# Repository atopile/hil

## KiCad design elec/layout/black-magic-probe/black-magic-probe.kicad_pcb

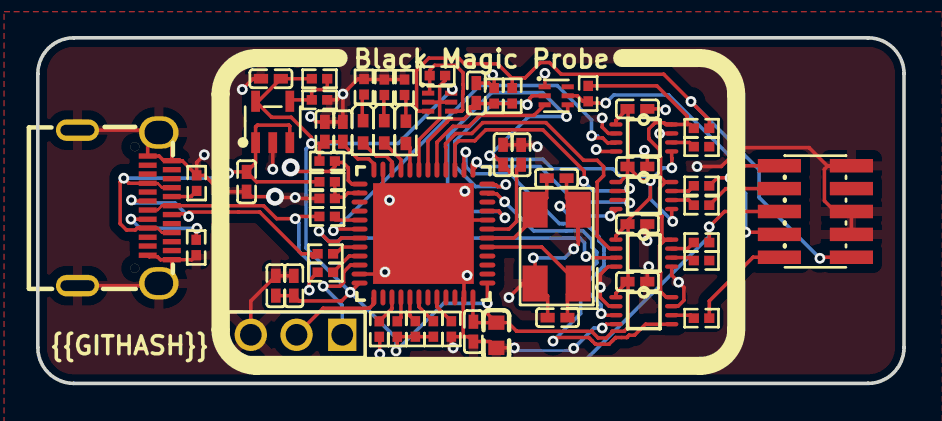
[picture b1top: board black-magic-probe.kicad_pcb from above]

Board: 2 copper layers, 48.1 x 19.2 mm, 61 parts (0 on the bottom side), 54 nets.

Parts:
C1, C2, C3, C4, C7, C8, C9, C10, C11, C12: 100nF ±10% 50V X7R; C0402-b3ef17
C5: 4.7µF ±10% 25V X5R; C0603-bd72f6
C6, C16, C17: 1µF ±10% 25V X5R; C0402-b3ef17
C13, C14: 18pF ±5% 50V C0G; C0402-b3ef17
C15: 100nF ±10% 16V X7R; C0402-b3ef17
D1, D2, D3: LED0402-R-RD-049f90
H1: HDR-TH_3P-P2.54-V-M-1-04b1f3
R1, R2, R3, R7, R11, R12, R13, R21, R23: 10kΩ ±1% 62.5mW; R0402-56259e
R4, R5, R6, R26: 1kΩ ±1% 62.5mW; R0402-56259e
R8: 1.5kΩ ±1% 62.5mW; R0402-56259e
R9, R10: 22Ω ±1% 62.5mW; R0402-56259e
R14, R15, R16, R17, R18, R19, R20, R25: 100Ω ±1% 62.5mW; R0402-56259e
R22, R24: 4.7kΩ ±1% 62.5mW; R0402-56259e
R27: 1.8kΩ ±1% 62.5mW; R0402-56259e
R28, R29: 5.1kΩ ±1% 62.5mW; R0402-56259e
U1, U2, U3, U4: VSSOP-8_L2.4-W2.1-P0.50-LS3.2-BR-acd3fc
U5: UFQFPN-48_L7.0-W7.0-P0.50-BL-EP5.6-10abf8
U6, U7: SOT-563-6_L1.6-W1.2-P0.5-LS1.6-BL-d9216f
U8: HDR-SMD_10P-P1.27-V-M-R2-C5-LS5.3-41d9cc
U9: SOT-23-5_L3.0-W1.7-P0.95-LS2.8-BL
USB1: USB-C-SMD_TYC-324G-a50b79
X1: OSC-SMD_4P-L5.0-W3.2-BL-ee849f

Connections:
ADJ_NC: R26.1, R27.2, U9.4
B5: R29.1, USB1.B5
BOOT0: R7.1, U5.44
CC1: R28.1, USB1.A5
D1: U5.17, U7.3
DIR: U4.5, U5.11
G1: R13.2, U7.5, U8.10
NRST: C12.1, U5.7
PA8: R8.2, U5.29
PA11: R9.2, U5.32
PA12: R10.2, U5.33
PA13: H1.1, U5.34
PA14: H1.2, U5.37
PB3: R18.1, U5.39
PB4: R1.1, U5.40
PB5: R2.1, U5.41
PB6: R3.1, U5.42
PB12: R11.1, U5.25
S1: R12.2, U6.1, U6.4
VCCB: R13.1, R25.1, U1.8, U2.8, U3.8, U4.8
black_magic_debugger-B1: R16.1, U3.7
black_magic_debugger-B1-1: R14.1, U2.7
black_magic_debugger-B2: R20.1, U1.6
black_magic_debugger-B2-1: R17.1, U4.6
black_magic_debugger-B2-2: R15.1, U2.6
black_magic_debugger-B2-3: R19.1, U3.6
black_magic_debugger-G2: U5.12, U7.2
black_magic_debugger-G2-1: R12.1, U5.19, U6.2, U6.5
black_magic_debugger-anode: D1.1, U5.20
black_magic_debugger-anode-1: D3.1, U5.22
black_magic_debugger-anode-2: D2.1, U5.21
black_magic_debugger-line: U2.3, U5.13
black_magic_debugger-line-1: U2.2, U5.15
black_magic_debugger-line-2: C15.1, R23.1, R24.2, U5.18
black_magic_debugger-line-3: U3.2, U5.16
black_magic_debugger-line-4: U1.3, U5.30
black_magic_debugger-line-5: R21.1, R22.2, U5.26
black_magic_debugger-line-8: U3.3, U5.31
black_magic_debugger-line-9: U4.3, U5.14
black_magic_debugger.led0-cathode: D1.2, R4.1
black_magic_debugger.led1-cathode: D2.2, R5.1
black_magic_debugger.led2-cathode: D3.2, R6.1
gnd: C1.2, C2.2, C3.2, C4.2, C5.2, C6.2, C7.2, C8.2, C9.2, C10.2, C11.2, C12.2, C13.2, C14.2, C15.2, C16.2, C17.2, H1.3, R4.2, R5.2, R6.2, R7.2, R21.2, R23.2, R26.2, R28.2, R29.2, U1.2, U1.4, U1.7, U2.4, U3.4, U3.5, U4.2, U4.4, U4.7, U5.8, U5.23, U5.35, U5.47, U5.49, U7.1, U8.3, U8.5, U8.9, U9.2, USB1.1, USB1.2, USB1.3, USB1.4, USB1.A1, USB1.A12, USB1.B1, USB1.B12, X1.2, X1.4
hv: C16.1, R22.1, U9.1, U9.3, USB1.A4, USB1.A9, USB1.B4, USB1.B9
hv-1: R24.1, R25.2, U6.3, U8.1
hv-2: C1.1, C2.1, C3.1, C4.1, C5.1, C6.1, C7.1, C8.1, C9.1, C10.1, C11.1, C17.1, R1.2, R2.2, R3.2, R11.2, R27.1, U1.1, U1.5, U2.1, U2.5, U3.1, U4.1, U5.1, U5.9, U5.24, U5.36, U5.48, U6.6, U7.4, U9.5
line: R17.2, U8.2
line-1: R9.1, USB1.A7, USB1.B7
line-2: R16.2, R18.2, U8.6
line-3: R14.2, U8.4
line-4: R15.2, U8.8
line-5: R8.1, R10.1, USB1.A6, USB1.B6
xin: C13.1, U5.5, X1.1
xout: C14.1, U5.6, X1.3

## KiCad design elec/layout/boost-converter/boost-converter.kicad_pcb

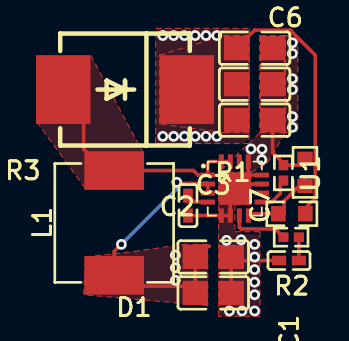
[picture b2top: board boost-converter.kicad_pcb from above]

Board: 2 copper layers, 14 parts (0 on the bottom side), 9 nets.

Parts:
C1: 6.8nF ±10% 50V X7R; C0402-b3ef17
C2, C3, C4, C5, C6: 10µF ±10% 25V X5R; C0805-3b2e55
C7: 4.7µF ±20% 6.3V X5R; C0402-b3ef17
D1: SMC_L7.1-W6.2-LS8.1-RD-d9649d
L1: IND-SMD_L7.1-W6.6-48b69f
R1: 10kΩ ±1% 100mW; R0603-ebcab9
R2: 180kΩ ±1% 100mW; R0603-ebcab9
R3: 2.49kΩ ±1% 62.5mW; R0402-56259e
R4: 75kΩ ±1% 62.5mW; R0402-56259e
U1: VQFN-16_L3.0-W3.0-P0.50-BL-EP1.7-62c35a

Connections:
COMP: R3.1, U1.7
FB: R1.1, R2.2, U1.8
FREQ: R4.1, U1.9
SS: C7.1, U1.4
gnd: C1.2, C2.2, C3.2, C4.2, C5.2, C6.2, C7.2, R1.2, R4.2, U1.5, U1.6, U1.11, U1.12, U1.13, U1.17
hv: C2.1, C3.1, L1.1, U1.2, U1.3
hv-1: C4.1, C5.1, C6.1, D1.1, R2.1
net: C1.1, R3.2
switching_node: D1.2, L1.2, U1.1, U1.15, U1.16

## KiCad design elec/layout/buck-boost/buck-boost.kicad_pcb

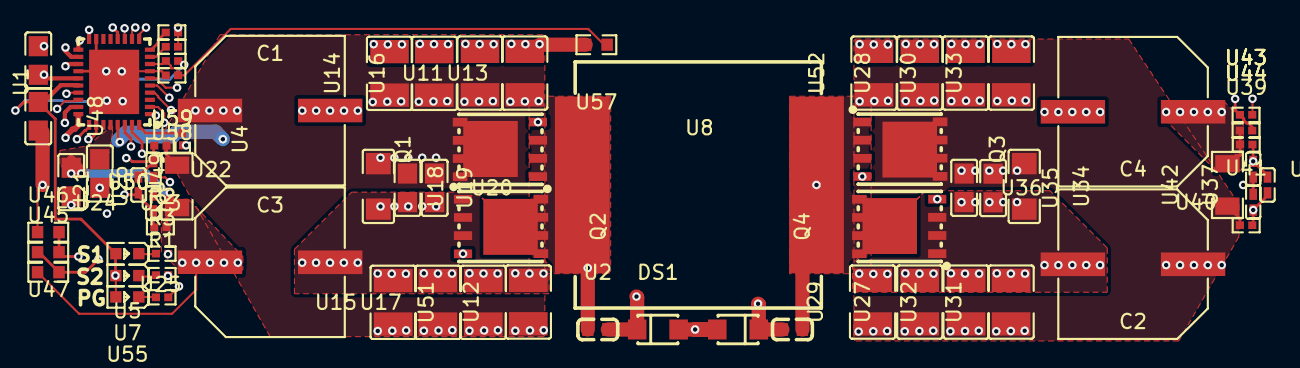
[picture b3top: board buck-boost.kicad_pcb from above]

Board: 6 copper layers, 69 parts (0 on the bottom side), 33 nets.

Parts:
C1, C2, C3, C4: 68µF ±20%; CAP-SMD_BD10.0-L10.3-W10.3-LS11.6-FD-b102ff
DS1, DS2: DO-219AB_L2.8-W1.8-LS3.7-RD-212ba1
Q1, Q2, Q3, Q4: POWERVDFN-8_L5.8-W4.9-P1.27-LS6.2-BL-167b96
R1, R2, R3: 2.7kΩ ±1% 62.5mW; R0402-56259e
U1: TQFN-36_L6.0-W5.0-P0.50-BL-EP-1-2fce41
U2, U3: 100nF ±10% 50V X7R; C0603-bd72f6
U4: 49.9kΩ ±0% 62.5mW; R0402-56259e
U5, U7, U55: LED0603-RD-c81ffb
U8: IND-SMD_L17.2-W17.2-132628
U9, U48: 4.7µF ±10% 25V X5R; C0805-3b2e55
U10: 2.49kΩ ±1% 62.5mW; R0402-56259e
U11, U12, U13, U27, U28, U29, U51, U52: 4.7µF ±10% 100V X7R; C1210-c93926
U14, U15, U16, U17, U30, U31, U32, U33: 10µF ±10% 100V X7R; C1210-c93926
U18, U34: 1µF ±10% 100V X7R; C1206-f0a137
U19, U35, U49: 100nF ±10% 100V X7R; C0805-3b2e55
U20, U36: 100pF ±5% 100V C0G; C0805-3b2e55
U21, U37: 470nF ±20% 16V X5R; C0402-b3ef17
U22, U24, U38, U40: 100nF ±10% 16V X7R; C0402-b3ef17
U23, U25, U39, U41: 10Ω ±1% 62.5mW; R0402-56259e
U26, U42: 5mΩ ±1% 1W; R1206-bdb864
U43: 13.7kΩ ±1% 62.5mW; R0402-56259e
U44: 249kΩ ±1% 62.5mW; R0402-56259e
U45: 1MΩ ±1% 100mW; R0603-ebcab9
U46: 133kΩ ±1% 100mW; R0603-ebcab9
U47: 25.5kΩ ±1% 100mW; R0603-ebcab9
U50: 1µF ±10% 100V X7S; C0805-3b2e55
U54: 0Ω 62.5mW; R0402-56259e
U57: R0603-ebcab9
U58: 30.1kΩ ±1% 62.5mW; R0402-56259e
U59: 5.23kΩ ±1% 62.5mW; R0402-56259e

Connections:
ACN: U1.29, U21.2, U22.1, U23.2
ACOV: U1.35, U46.2, U47.1
ACP: U1.30, U21.1, U24.1, U25.2
ACUV: U1.34, U45.2, U46.1
FB: U1.12, U43.1, U44.2
FSW_SYNC: U1.36, U4.1
ICHG: U1.9, U54.1
ILIM_HIZ: U1.10, U10.1
SRN: U1.13, U37.2, U38.1, U39.2
SRP: U1.14, U37.1, U40.1, U41.2
TS: U1.8, U57.1, U58.1, U59.2
anode: DS1.2, DS2.2, U1.23, U9.1
anode-1: U1.24, U5.2, U7.2, U48.1, U55.2, U59.1
cathode: DS2.1, U1.20, U3.2
cathode-1: DS1.1, U1.26, U2.2
gate: Q3.4, U1.19
gate-1: Q2.4, U1.25
gate-2: Q1.4, U1.27
gate-3: Q4.4, U1.21
gnd: R2.2, U1.4
gnd-1: U1.11, U43.2
gnd-2: R3.2, U1.5
gnd-3: R1.2, U1.6
gnd-4: C1.2, C2.2, C3.2, C4.2, Q2.1, Q2.2, Q2.3, Q4.1, Q4.2, Q4.3, U1.7, U1.17, U1.22, U1.37, U4.2, U9.2, U10.2, U11.2, U12.2, U13.2, U14.2, U15.2, U16.2, U17.2, U18.2, U19.2, U20.2, U22.2, U24.2, U27.2, U28.2, U29.2, U30.2, U31.2, U32.2, U33.2, U34.2, U35.2, U36.2, U38.2, U40.2, U47.2, U48.2, U49.2, U50.2, U51.2, U52.2, U54.2, U57.2, U58.2
hv: C4.1, U1.33, U39.1, U42.2, U44.1
hv-1: C3.1, U1.32, U25.1, U26.1, U45.1, U49.1, U50.1
hv-2: C1.1, Q1.5, Q1.6, Q1.7, Q1.8, U11.1, U12.1, U13.1, U14.1, U15.1, U16.1, U17.1, U18.1, U19.1, U20.1, U23.1, U26.2, U51.1
hv-3: C2.1, Q3.5, Q3.6, Q3.7, Q3.8, U27.1, U28.1, U29.1, U30.1, U31.1, U32.1, U33.1, U34.1, U35.1, U36.1, U41.1, U42.1, U52.1
pg_status_led-cathode: R1.1, U55.1
source: Q1.1, Q1.2, Q1.3, Q2.5, Q2.6, Q2.7, Q2.8, U1.28, U2.1, U8.1
source-1: Q3.1, Q3.2, Q3.3, Q4.5, Q4.6, Q4.7, Q4.8, U1.18, U3.1, U8.2
status_1_led-cathode: R2.1, U5.1
status_2_led-cathode: R3.1, U7.1

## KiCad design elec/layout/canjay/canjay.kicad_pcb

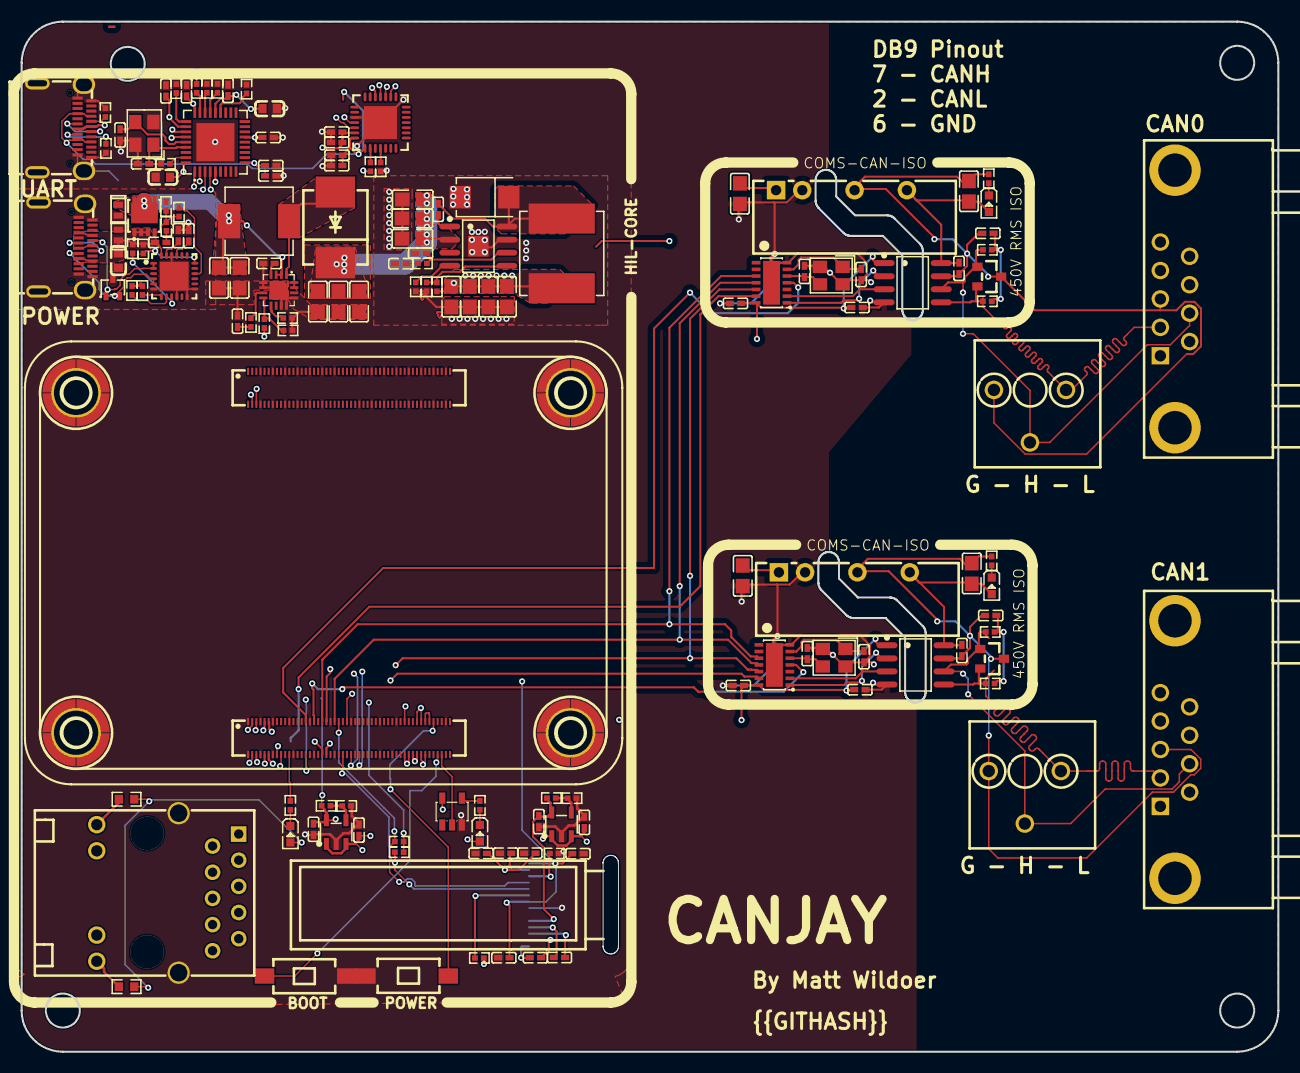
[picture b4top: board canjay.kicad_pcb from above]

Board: 6 copper layers, 122.0 x 100.0 mm, 153 parts (0 on the bottom side), 114 nets.

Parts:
C1, C7, C8, C9, C15, C16, C27, C28, C51, C55, C56: 1µF ±10% 25V X5R; C0402-b3ef17
C2, C3, C10, C11: 10pF ±5% 50V C0G; C0402-b3ef17
C4, C12: 2.2µF ±10% 50V X5R; C0805-3b2e55
C5, C13, C18, C19, C20, C21, C22: 10µF ±10% 25V X5R; C0805-3b2e55
C6, C14: 4.7nF ±10% 50V X7R; C0402-b3ef17
C17: 6.8nF ±10% 50V X7R; C0402-b3ef17
C23, C30, C53: 4.7µF ±20% 10V X5R; C0402-b3ef17
C24: 100nF ±10% 50V X7R; C0402-b3ef17
C25: 4.7nF ±5% 50V C0G; C0402-b3ef17
C26: 8.2pF ±5% 50V C0G; C0402-b3ef17
C29, C31, C32, C33, C36, C37, C38, C39, C40, C41, C50, C52, C57: 100nF ±10% 16V X7R; C0402-b3ef17
C34, C35: 10µF ±10% 10V X5R; C0603-bd72f6
C42, C43: 20pF ±5% 50V C0G; C0402-b3ef17
C44, C45, C46: 10µF ±10% 50V X5R; C0805-3b2e55
C47, C48, C49, C58: 22µF ±20% 25V X5R; C0805-3b2e55
C54: 4.7µF ±10% 35V X5R; C0603-bd72f6
CN1, CN2: CONN-TH_3P-P3.50_MX250-3.5-03P-B-GY01-CU-A-de886a
CN3, CN4: CONN-SMD_DF40C-100DS-0.4V-51-ceffa9
D1, D2: SOT-23_L2.9-W1.3-P1.90-LS2.4-BR-0c2373
D3: SMC_L7.1-W6.2-LS8.1-RD-d9649d
D4: LED0603-RD-YELLOW-5af84a
D5, D15, D16: LED0603-RD-c81ffb
D12: SOT-323-3_L2.1-W1.3-P1.32-LS2.1-BR-ee9edb
D13, D14: DFN1610-2_L1.6-W1.0-P1.05-RD-57a24e
DSub1, DSub2: DSUB-TH_DMR-9P-42a645
L1: IND-SMD_L7.1-W6.6-48b69f
OLED1: OLED-SMD_N087-2832TSWYG02-H14_1-7d3a70
Q1: PDFN3333-8_L3.1-W3.2-P0.65-LS3.4-BL-33e04e
R1, R2, R3, R4: 1MΩ ±1% 62.5mW; R0402-56259e
R5, R9, R24, R36, R37, R38, R39: 10kΩ ±1% 62.5mW; R0402-56259e
R6: 180kΩ ±1% 62.5mW; R0402-56259e
R7: 2.49kΩ ±1% 62.5mW; R0402-56259e
R8: 75kΩ ±1% 62.5mW; R0402-56259e
R10: 51kΩ ±1% 62.5mW; R0402-56259e
R11, R12: 2kΩ ±1% 62.5mW; R0402-56259e
R13, R14: 470Ω ±1% 100mW; R0603-ebcab9
R15: 510kΩ ±1% 62.5mW; R0402-56259e
R16, R17: 5.1kΩ ±1% 62.5mW; R0402-56259e
R18, R19, R21, R22: 33kΩ ±1% 62.5mW; R0402-56259e
R20: 12kΩ ±1% 62.5mW; R0402-56259e
R23: 23.7kΩ ±1% 62.5mW; R0402-56259e
R25, R27, R28: 4.7kΩ ±1% 62.5mW; R0402-56259e
R26, R29: 1kΩ ±1% 62.5mW; R0402-56259e
R30: 100kΩ ±1% 62.5mW; R0402-56259e
R31: 22kΩ ±1% 62.5mW; R0402-56259e
R32: 100Ω ±1% 62.5mW; R0402-56259e
R33, R34: 2.2kΩ ±1% 62.5mW; R0402-56259e
R35: 162kΩ ±1% 62.5mW; R0402-56259e
RJ1: RJ45-TH_HR911130A-5845d4
SW1, SW2: SW-SMD_L6.0-W3.3-LS8.0-cfbaed
U1, U5: VDFN-14_L4.5-W3.0-P0.65-BL-EP-99cb5b
U2, U6: CRYSTAL-SMD_4P-L3.2-W2.5-BL-e199c8
U3, U7: PWRM-TH_BXXXXS-2WR3-d8b2fb
U4, U8: SOIC-8_L4.9-W3.9-P1.27-LS6.0-BL-6ccfeb
U9: VQFN-16_L3.0-W3.0-P0.50-BL-EP1.7-62c35a
U10: SMB_L4.6-W3.6-LS5.3-RD-330cb3
U11: SOIC-8_L5.0-W4.0-P1.27-LS6.0-BL-EP2.0-748c0f
U12: 10µH ±20%; IND-SMD_L8.0-W8.0_SWPA8040S-2a70f8
U13: SOT-23-5_L3.0-W1.7-P0.95-LS2.8-BR-9d80aa
U14, U15, U16, U17: SMD_BD5.6-D4.1-12eb58
U18, U23: 10kΩ ±1% 62.5mW; R0402-56259e
U19: 18kΩ ±1% 62.5mW; R0402-56259e
U20, U22, U25, U27: 1µF ±10% 25V X5R; C0402-b3ef17
U21, U26: SOT-23-5_L3.0-W1.7-P0.95-LS2.8-BL
U24: 25.5kΩ ±1% 62.5mW; R0402-56259e
U28: SQFN-36_L6.0-W6.0-P0.50-BL-EP-5817ac
U30: WQFN-28_L5.0-W5.0-P0.50-BL-EP3.2-79d8c5
U31: QFN-24_L4.0-W4.0-P0.50-BL-EP2.8-2a85a7
U32: NetTie-2_SMD_Pad0.25mm
USB1, USB2: USB-C-SMD_TYC-324G-a50b79
X1: CRYSTAL-SMD_4P-L3.2-W2.5-BL-1-d85bc6

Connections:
A7: USB2.A7, USB2.B7
BOOT: C24.1, U11.1
C1N: C27.1, OLED1.4
C1P: C27.2, OLED1.3
C2N: C28.1, OLED1.2
C2P: C28.2, OLED1.1
CANH: CN2.2, D2.1, DSub2.7, R3.1, U8.6
CANH-1: CN1.2, D1.1, DSub1.7, R1.1, U4.6
CANL: CN1.1, D1.2, DSub1.2, R2.2, U4.5
CANL-1: CN2.1, D2.2, DSub2.2, R4.2, U8.5
CC1: R16.1, USB1.A5
CC2: R17.1, USB1.B5
DISCH: R26.2, U31.9
DP1: USB2.A6, USB2.B6
Dminus: U28.1, U30.5
Dplus: U28.2, U30.4
FREQ: R8.1, U9.9
GND: C1.2, C2.2, C3.2, C4.2, C7.2, C9.2, C10.2, C11.2, C12.2, C15.2, C17.2, C18.2, C19.2, C20.2, C21.2, C22.2, C23.2, C25.2, C26.2, C29.2, C30.2, C31.2, C32.2, C33.2, C34.2, C35.2, C36.2, C37.2, C38.2, C39.2, C40.2, C41.2, C42.2, C43.2, C44.2, C45.2, C46.2, C47.2, C48.2, C49.2, C50.2, C51.2, C52.2, C53.2, C54.1, C55.1, C56.1, C58.2, CN3.1, CN3.4, CN3.7, CN3.11, CN3.16, CN3.21, CN3.26, CN3.30, CN3.33, CN3.37, CN3.49, CN3.65, CN3.68, CN3.71, CN3.74, CN3.79, CN3.84, CN3.89, CN3.94, CN3.97, CN3.100, CN4.4, CN4.7, CN4.10, CN4.13, CN4.16, CN4.19, CN4.22, CN4.28, CN4.31, CN4.34, CN4.37, CN4.40, CN4.43, CN4.46, CN4.49, CN4.52, CN4.55, CN4.58, CN4.61, CN4.64, CN4.67, CN4.70, CN4.73, CN4.82, CN4.85, CN4.88, CN4.91, CN4.94, CN4.97, D12.3, D13.2, D14.2, OLED1.7, R5.2, R8.2, R9.2, R15.2, R16.2, R17.2, R18.2, R19.2, R20.2, R21.2, R22.2, R24.2, R35.2, RJ1.SHIELD0, RJ1.SHIELD1, SW1.2, SW2.2, U1.7, U1.15, U2.2, U2.4, U3.2, U4.4, U5.7, U5.15, U6.2, U6.4, U7.2, U8.4, U9.5, U9.6, U9.11, U9.12, U9.13, U9.17, U10.2, U11.7, U11.9, U13.3, U14.1, U14.2, U14.3, U14.4, U15.1, U15.2, U15.3, U15.4, U16.1, U16.2, U16.3, U16.4, U17.1, U17.2, U17.3, U17.4, U18.2, U20.2, U21.2, U22.2, U23.2, U25.2, U26.2, U27.2, U28.37, U30.3, U30.29, U31.6, U31.10, U31.12, U31.13, U31.22, U31.25, USB1.1, USB1.2, USB1.3, USB1.4, USB1.A1, USB1.A12, USB1.B1, USB1.B12, USB2.1, USB2.2, USB2.3, USB2.4, USB2.A1, USB2.A12, USB2.B1, USB2.B12, X1.2, X1.4
HS_IND_CFG_SEL1: R21.1, U28.25
INTh: CN3.15, U1.4
INTh-1: CN3.17, U5.4
IREF: OLED1.12, R15.1
MDI0plus: CN3.6, RJ1.P2
MDI1plus: CN3.2, RJ1.P4
MDI2plus: CN3.95, RJ1.P5
MDI3_: CN3.98, RJ1.P9
MDI3plus: CN3.99, RJ1.P8
POWER_3V3: C1.1, C7.1, C9.1, C15.1, C29.1, C30.1, C31.1, C32.1, C33.1, C34.1, C35.1, C36.1, C37.1, C38.1, C39.1, C40.1, C41.1, CN3.39, CN3.42, CN3.43, D4.2, D5.2, OLED1.8, OLED1.13, OLED1.14, R13.1, R14.1, R36.2, R37.2, R38.2, R39.2, U1.14, U4.1, U5.14, U8.1, U13.5, U19.1, U21.5, U22.1, U28.5, U28.10, U28.15, U28.23, U28.27, U28.29, U28.36
POWER_5V: C4.1, C12.1, C47.1, C48.1, C49.1, C58.1, CN3.57, CN3.58, CN3.59, CN3.60, CN3.61, CN3.62, R10.1, U3.1, U7.1, U12.2, U20.1, U21.1, U21.3, U25.1, U26.1, U26.3
POWER_24V: C20.1, C21.1, C22.1, C44.1, C45.1, C46.1, D3.1, R6.1, U11.2
RBIAS: R20.1, U28.35
RESET_N: R39.1, U28.26
RESh: OLED1.9, R38.1
RSTh: R25.1, U30.9
RT_CLK: R35.1, U11.4
SCK: CN3.19, U1.10, U5.10
SCL_SMBCLK_CFG_SEL0: R18.1, U28.24
SDA_SMBBATA_NON_REM1: R19.1, U28.22
SDI: CN3.22, U1.11, U5.11
SDO: CN3.20, U1.12, U5.12
SS: C23.1, U9.4
SUSPENDh: R24.1, U30.11
SUSP_IND_LOCAL_PWR_NON_REM0: R22.1, U28.28
SW: C24.2, U10.1, U11.8, U12.1
USBDM_UP: U28.30, USB1.A7, USB1.B7
USBDP_UP: U28.31, USB1.A6, USB1.B6
VBUS: C54.2, C57.2, D13.1, Q1.1, Q1.2, Q1.3, R26.1, R29.1, U31.24, USB2.A4, USB2.A9, USB2.B4, USB2.B9
VBUS_EN_SNK: R31.2, U31.16
VBUS_VS_DISCH: R29.2, U31.18
Y: R12.2, U13.4
can0-rx: U1.2, U4.3
can0-tx: U1.1, U4.2
can0.regulator.led-cathode: D15.1, R33.1
can0.termination-_midpoint: C6.1, R1.2, R2.1
can1-rx: U5.2, U8.3
can1-tx: U5.1, U8.2
can1.regulator.led-cathode: D16.1, R34.1
can1.termination-_midpoint: C14.1, R3.2, R4.1
gate: Q1.4, R30.1, R31.1, R32.1
gnd: C5.2, C6.2, C8.2, CN1.3, D1.3, DSub1.3, R33.2, U3.4, U4.7
gnd-1: C13.2, C14.2, C16.2, CN2.3, D2.3, DSub2.3, R34.2, U7.4, U8.7
hil_core-line: CN3.86, U30.24
hil_core-line-1: CN3.75, U30.26
hil_core-line-2: CN3.77, OLED1.10, R36.1
hil_core-line-3: CN3.25, U30.23
hil_core-line-4: CN3.73, U30.25
hil_core-line-5: CN3.23, OLED1.11, R37.1
hil_core.boost_24v-COMP: R7.1, U9.7
hil_core.boost_24v-FB: R5.1, R6.2, U9.8
hil_core.boost_24v-net: C17.1, R7.2
hil_core.buck_5v-COMP: C26.1, R23.1, U11.6
hil_core.buck_5v-FB: R9.1, R10.2, U11.5
hil_core.buck_5v-net: C25.1, R23.2
hil_core.controller-pins[5]: CN3.3, RJ1.P7
hil_core.controller-pins[8]: CN3.96, RJ1.P6
hil_core.controller-pins[9]: CN3.5, RJ1.P3
hil_core.controller-pins[14]: CN3.93, RJ1.12
hil_core.controller-pins[16]: CN3.92, RJ1.13
hil_core.controller-pins[92]: CN3.54, SW1.1
hil_core.controller.cm5-cathode: D5.1, R12.1
hil_core.controller.cm5-cathode-1: D4.1, R11.1
hil_core.controller.cm5-pins[20]: CN3.90, R11.2
hil_core.controller.cm5-pins[89]-1: CN3.44, CN3.45
hil_core.controller.cm5-pins[94]: CN3.53, U13.2
hil_core.controller.rj45-anode: R14.2, RJ1.14
hil_core.controller.rj45-anode-1: R13.2, RJ1.11
hil_core.ldo_3v3-ADJ_NC: U18.1, U19.2, U21.4
hil_core.oled.regulator_4v-ADJ_NC: U23.1, U24.2, U26.4
hil_core.usbpd-hv: R27.2, R28.2
hil_core.usbpd-line: D12.1, U31.1, U31.2, USB2.A5
hil_core.usbpd-line-1: R27.1, U31.7
hil_core.usbpd-line-2: R28.1, U31.8
hil_core.usbpd-line-3: D12.2, U31.4, U31.5, USB2.B5
hil_core.usbpd.pd_controller-hv: C56.2, U31.23
hil_core.usbpd.pd_controller-hv-1: C55.2, U31.21
hil_core.usbpd.pd_controller-net: C57.1, R32.2
hv: C13.1, C16.1, D16.2, U7.6, U8.8
hv-1: C50.1, C51.1, U30.7, U30.8, USB1.A4, USB1.A9, USB1.B4, USB1.B9
hv-2: OLED1.5, U24.1, U26.5, U27.1
hv-3: C52.1, C53.1, R25.2, U30.6
hv-4: C18.1, C19.1, D14.1, L1.1, Q1.5, Q1.6, Q1.7, Q1.8, Q1.9, R30.2, U9.2, U9.3
hv-5: C5.1, C8.1, D15.2, U3.6, U4.8
line: CN3.81, U1.13
line-1: CN3.82, U5.13
pins[2]: CN4.99, U28.3
pins[4]: CN4.98, U28.4
pins[91]: CN3.46, SW2.1
switching_node: D3.2, L1.2, U9.1, U9.15, U9.16
xin: C2.1, U1.6, U2.1
xin-1: C42.1, U28.33, X1.1
xin-2: C10.1, U5.6, U6.1
xout: C11.1, U5.5, U6.3
xout-1: C3.1, U1.5, U2.3
xout-2: C43.1, U28.32, X1.3

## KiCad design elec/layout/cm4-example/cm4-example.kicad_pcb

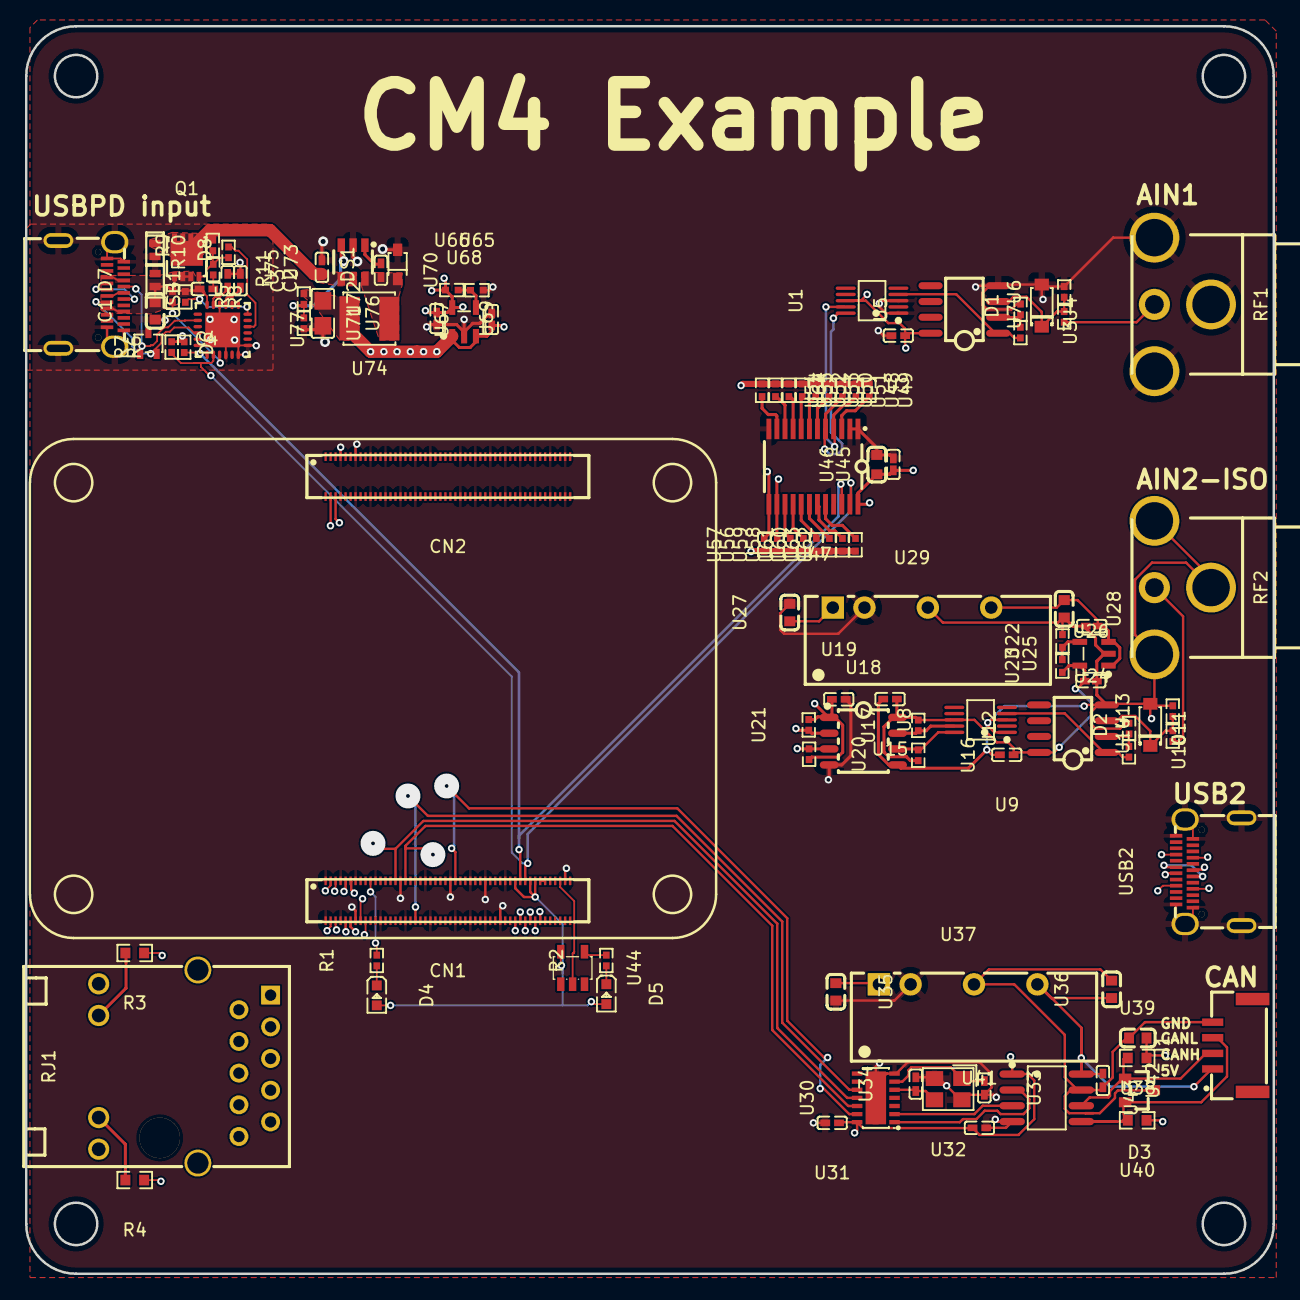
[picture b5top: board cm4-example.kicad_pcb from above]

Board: 4 copper layers, 100.0 x 100.0 mm, 110 parts (0 on the bottom side), 89 nets.

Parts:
C1: 4.7µF ±10% 35V X5R; C0603-bd72f6
C2, C3: 1µF ±10% 25V X5R; C0402-b3ef17
C4: 100nF ±10% 16V X7R; C0402-b3ef17
CN1, CN2: CONN-SMD_DF40C-100DS-0.4V-51-ceffa9
D1, D2: SOD-123_L2.8-W1.8-LS3.7-RD-5bef17
D3: SOT-23_L2.9-W1.3-P1.90-LS2.4-BR-0c2373
D4: LED0603-RD-YELLOW-5af84a
D5: LED0603-RD-c81ffb
D6: SOT-323-3_L2.1-W1.3-P1.32-LS2.1-BR-ee9edb
D7, D8: DFN1610-2_L1.6-W1.0-P1.05-RD-57a24e
DS1: SOD-323_L1.8-W1.3-LS2.5-RD
J1: CONN-SMD_4P-P1.25_SM04B-GHS-TB-LF-SN
Q1: PDFN3333-8_L3.1-W3.2-P0.65-LS3.4-BL-33e04e
R1, R2, R5, R8: 1kΩ ±1% 62.5mW; R0402-56259e
R3, R4: 470Ω ±1% 100mW; R0603-ebcab9
R6, R7: 4.7kΩ ±1% 62.5mW; R0402-56259e
R9: 100kΩ ±1% 62.5mW; R0402-56259e
R10: 22kΩ ±1% 62.5mW; R0402-56259e
R11: 100Ω ±1% 62.5mW; R0402-56259e
RF1, RF2: BNC-TH_DOSIN-801-0072-4dbc44
RJ1: RJ45-TH_HR911130A-5845d4
U1, U8: MSOP-10_L3.0-W3.0-P0.50-LS5.0-BL
U2, U9, U24, U26, U31, U41, U42, U67, U69: 1µF ±10% 25V X5R; C0402-b3ef17
U3, U4, U10, U11, U16, U17, U20, U21, U48, U49, U50, U51, U52, U53, U54, U55, U56, U57, U58, U59, U60, U61, U62, U63, U64: 10kΩ ±1% 62.5mW; R0402-56259e
U5, U12: SOIC-8_L5.0-W4.0-P1.27-LS6.0-BL-294f77
U6, U7, U13, U14, U22, U23, U65, U66, U71, U72: 1kΩ ±1% 62.5mW; R0402-56259e
U15, U19, U45: 100nF ±10% 16V X7R; C0402-b3ef17
U18: SOIC-8_L4.9-W3.9-P1.27-LS6.0-TL
U25, U68: SOT-23-5_L3.0-W1.7-P0.95-LS2.8-BL
U27, U35: 4.7µF ±10% 10V X5R; C0603-bd72f6
U28, U36: 10µF ±10% 10V X5R; C0603-bd72f6
U29, U37: PWRM-TH_BXXXXS-2WR3-d8b2fb
U30: VDFN-14_L4.5-W3.0-P0.65-BL-EP-99cb5b
U32: CRYSTAL-SMD_4P-L3.2-W2.5-BL-e199c8
U33, U34: 10pF ±5% 50V C0G; C0402-b3ef17
U38: 4.7nF ±10% 50V X7R; C0603-bd72f6
U39, U40: 60.4Ω ±1% 100mW; R0603-ebcab9
U43: SOIC-8_L4.9-W3.9-P1.27-LS6.0-BL-6ccfeb
U44: SOT-23-5_L3.0-W1.7-P0.95-LS2.8-BR-9d80aa
U46: 2.2µF ±10% 25V X5R; C0603-bd72f6
U47: TSSOP-24_L7.8-W4.4-P0.65-LS6.4-BL
U70: 470nF ±20% 16V X5R; C0402-b3ef17
U73: SOT-23-6_L2.9-W1.6-P0.95-LS2.8-BR
U74: IND-SMD_L4.0-W4.0
U75: 2.2µF ±20% 6.3V X5R; C0402-b3ef17
U76: 10µF ±10% 25V X5R; C0805-3b2e55
U77: QFN-24_L4.0-W4.0-P0.50-BL-EP2.8-2a85a7
USB1, USB2: USB-C-SMD_TYC-324G-a50b79

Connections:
CANH: D3.1, J1.2, U39.1, U43.6
CANL: D3.2, J1.3, U40.2, U43.5
CB: U70.1, U73.1
CC1: D6.1, U77.2, USB1.A5
CC2: D6.2, U77.4, USB1.B5
DISCH: R5.2, U77.9
ETH_LED_ACTIVITY: CN1.92, RJ1.14
ETH_LED_LINK: CN1.93, RJ1.11
ETH_P0_N: CN1.5, RJ1.P3
ETH_P0_P: CN1.6, RJ1.P2
ETH_P1_N: CN1.3, RJ1.P7
ETH_P1_P: CN1.2, RJ1.P4
ETH_P2_N: CN1.96, RJ1.P6
ETH_P2_P: CN1.95, RJ1.P5
ETH_P3_N: CN1.98, RJ1.P9
ETH_P3_P: CN1.99, RJ1.P8
GND: C1.1, C2.1, C3.1, CN1.1, CN1.4, CN1.7, CN1.11, CN1.16, CN1.21, CN1.26, CN1.30, CN1.33, CN1.37, CN1.49, CN1.65, CN1.68, CN1.71, CN1.74, CN1.79, CN1.84, CN1.89, CN1.90, CN1.94, CN1.97, CN1.100, CN2.4, CN2.7, CN2.10, CN2.13, CN2.16, CN2.19, CN2.22, CN2.28, CN2.31, CN2.34, CN2.37, CN2.40, CN2.43, CN2.46, CN2.49, CN2.52, CN2.55, CN2.58, CN2.61, CN2.64, CN2.67, CN2.70, CN2.73, CN2.82, CN2.85, CN2.88, CN2.91, CN2.94, CN2.97, D1.2, D6.3, D7.2, D8.2, DS1.2, RF1.2, RF1.3, RF1.4, U1.1, U1.3, U2.2, U4.1, U5.4, U6.2, U18.4, U19.2, U27.2, U29.2, U30.7, U30.15, U31.2, U32.2, U32.4, U33.2, U34.2, U35.2, U37.2, U41.2, U43.4, U45.2, U46.2, U47.1, U47.2, U47.12, U47.21, U65.2, U67.2, U68.2, U69.2, U71.2, U73.2, U75.2, U76.2, U77.6, U77.10, U77.12, U77.13, U77.22, U77.25, USB1.1, USB1.2, USB1.3, USB1.4, USB1.A1, USB1.A12, USB1.B1, USB1.B12, USB2.1, USB2.2, USB2.3, USB2.4, USB2.A1, USB2.A12, USB2.B1, USB2.B12
PWR_LED: CN1.48, U44.2
SCL: CN1.40, R6.1, U47.22, U77.7
SDA: CN1.41, R7.1, U47.23, U77.8
USB2_D_N: CN2.99, USB2.A6, USB2.B6
USB2_D_P: CN2.98, USB2.A7, USB2.B7
VBUS: C1.2, C4.2, D7.1, Q1.1, Q1.2, Q1.3, R5.1, R8.1, U77.24, USB1.A4, USB1.A9, USB1.B4, USB1.B9
VBUS_EN_SNK: R10.2, U77.16
VBUS_VS_DISCH: R8.2, U77.18
VCC_1V8: CN1.44, CN1.45
VCC_3V3: CN1.39, CN1.42, CN1.43, D4.2, D5.2, R3.1, R4.1, U44.5
VCC_5V: CN1.57, CN1.58, CN1.59, CN1.60, CN1.61, CN1.62, U27.1, U29.1, U35.1, U37.1, U67.1, U68.1, U68.3, U72.1, U74.2, U76.1, USB2.A4, USB2.A9, USB2.B4, USB2.B9
VREG_1V2: C2.2, U77.21
VREG_2V7: C3.2, U77.23
VSINK_VCC: D8.1, Q1.5, Q1.6, Q1.7, Q1.8, Q1.9, R9.2, U73.4, U73.5, U75.1
Y: R2.2, U44.4
_midpoint: U38.1, U39.2, U40.1
analog_in_2-line: U8.9, U17.1, U18.7
analog_in_2-line-1: U8.10, U16.1, U18.6
analog_in_2.regulator_3v3_isolated-out: U22.1, U23.2, U25.4
cathode: D1.1, U5.3, U6.1, U7.2
cathode-1: D2.1, U12.3, U13.1, U14.2
cathode-2: DS1.1, U70.2, U73.6, U74.1
controller.cm4-cathode: D5.1, R2.1
controller.cm4-cathode-1: D4.1, R1.1
controller.rj45-anode: R3.2, RJ1.12
controller.rj45-anode-1: R4.2, RJ1.13
cs: CN1.27, U30.13
dm: USB1.A7, USB1.B7
dp: USB1.A6, USB1.B6
gate: Q1.4, R9.1, R10.1, R11.1
gnd: D3.3, J1.4, U36.2, U37.4, U38.2, U42.2, U43.7
gnd-1: RJ1.SHIELD0, RJ1.SHIELD1
gnd-2: D2.2, RF2.2, RF2.3, RF2.4, U8.1, U8.3, U9.2, U11.1, U12.4, U13.2, U15.2, U18.5, U22.2, U24.2, U25.2, U26.2, U28.2, U29.4
hv: U24.1, U25.1, U25.3, U28.1, U29.6
hv-1: U8.8, U9.1, U12.8, U15.1, U16.2, U17.2, U18.8, U23.1, U25.5, U26.1
hv-2: J1.1, U36.1, U37.6, U42.1, U43.8
hv-3: U1.8, U2.1, U5.8, U18.1, U19.1, U20.2, U21.2, U30.14, U31.1, U41.1, U43.1, U45.1, U46.1, U47.24, U48.1, U49.1, U50.1, U51.1, U52.1, U53.1, U54.1, U55.1, U56.1, U57.1, U58.1, U59.1, U60.1, U61.1, U62.1, U63.1, U64.2, U66.1, U68.5, U69.1
i2c_multiplexer-io: U47.3, U64.1
i2c_multiplexer-line: U47.15, U59.2
i2c_multiplexer-line-1: U47.6, U51.2
i2c_multiplexer-line-2: U47.8, U53.2
i2c_multiplexer-line-3: U47.10, U55.2
i2c_multiplexer-line-4: U47.19, U63.2
i2c_multiplexer-line-5: U47.7, U50.2
i2c_multiplexer-line-6: U47.16, U58.2
i2c_multiplexer-line-7: U47.9, U52.2
i2c_multiplexer-line-8: U47.11, U54.2
i2c_multiplexer-line-9: U47.20, U62.2
i2c_multiplexer-line-10: U47.17, U61.2
i2c_multiplexer-line-11: U47.18, U60.2
inverting: U3.1, U4.2, U5.2
inverting-1: U10.1, U11.2, U12.2
io: RF2.1, U14.1
io-1: RF1.1, U7.1
line: U18.3, U20.1, U47.14, U56.2
line-1: U1.9, U47.4, U49.2
line-2: U18.2, U21.1, U47.13, U57.2
line-3: U1.10, U47.5, U48.2
miso: CN1.17, U30.12
mosi: CN1.15, U30.11
output: U8.4, U10.2, U12.1
output-1: U1.4, U3.2, U5.1
pins[19]: CN1.10, R1.2
regulator_3v3-out: U65.1, U66.2, U68.4
regulator_5v-out: U71.1, U72.2, U73.3
rx: U30.2, U43.3
sck: CN1.82, U30.10
tx: U30.1, U43.2
usb_pd-hv: R6.2, R7.2
usb_pd.pd_controller-net: C4.1, R11.2
xin: U30.6, U32.1, U33.1
xout: U30.5, U32.3, U34.1
